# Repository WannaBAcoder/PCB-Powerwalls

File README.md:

# PCB-Powerwalls
This is the public file Repository for the [DIY PCB Powerwalls Community](https://www.facebook.com/groups/2573968699280898/). The projects are developed and maintained by **Vinnie Maro** and **Shaun Bond**.

We are developing a PCB alternative to common powerwall building techniques for 18650(and similar) batteries. This system has been developed with maintainability, expandability, and practicality in mind. 

For additional DIY Powerwall building resources, please check out some of the many other active facebook groups and forums:
* [DIY Powerwalls](https://www.facebook.com/groups/323586824654552/)
* [Jehu's DIY Powerwalls](https://www.facebook.com/groups/183620862292017/)
* [DIY Powerwall - easy](https://www.facebook.com/groups/244099703167519/)
* [Second Life Storage](https://secondlifestorage.com/index.php)

## Features in Development
To see features currently in development or exploration, check out our [issues](https://github.com/WannaBAcoder/PCB-Powerwalls/issues) page.

## 15s4p PCB

The 15s4p battery board is a stackable solution that reduces the amount of wiring required by placing all series and balance connections through standoffs that structurally connect the boards. Batteries mount to both sides of the PCB, in a variety of ways. Each cell is individually fused for added safety.

### 1. Plastic battery holders

You can choose to use plastic cell holders that are available in many through-hole and surface mount packages. For the through-hole packages, you must bend the pins at a 90 degree angle so that the holders sit as flat as possible.

### 2. Spring clips

A cheaper alternative to plastic holders is spring clips. The clips work like traditional battery holders with springs, but these require the use of zip ties to hold the cells in place.

### 3. Fuse wire

The last option is to use fuse wire. You will still need to use zip ties to hold the cells in place, but you can solder the fuse wire directly to the PCB pads, and remove the need for populating fuses(you will need to short the fuse pads to do this). You can also use large fuse wire and still use fuses, if desired. Spotwelding fuse wire to the batteries and soldering the other end to the PCB pads is recommended.

### 7s Adapter PCB

The 7s Adapter PCB was created to take our popular 15s4p design and convert it into a 7s8p PCB. We do this by leaving the out the 8s cells, which creates two 7s groups that get connected in parallel. It is recommended to use at least one of these adapter PCBs for every 5 boards, or 20A of main fuse(which is 10A load on each of these boards). This board also joins the battery stacks with standoffs. It's important to equally space these boards within a pack for best current distribution. For example, a 12 battery board stack could use 3 adapter boards, spaced every 4 boards.

### BMS/Display Adapter PCB

The BMS/display adapter board helps the user connect a [Moonitor](https://www.sarperonal.com/product/6s-16s-solar-plc-li-ion-battery-protection-system/), or a variety of BMS systems to the battery PCB stacks, and is capable of supporting ~5A balance current. This board also includes spaces to add series-level voltage displays, but they can be disabled if not desired.  You can also use this board with the 7s adapter board configurations.

## Building Your Own

### Ordering the PCBs

You can order your own boards from any number of PCB manufacturers. Many of our supporters use [JLCPCB.com](https://jlcpcb.com/quote).

**Recommended manufacturing options:**
* PCB thickness - 1.6mm
* PCB color-Your choice (black is not available for 2oz copper orders)
* Surface finish - HASL(with lead)
* Copper weight - 1oz or 2oz **(Higher current applications use 2oz)**
* All other options can be left as default

### Ordering Parts
#### Common Parts
* M4 Standoffs(40mm for SMD plastic holders, 45mm for through-hole plastic holders, may be able to make 40mm work with zip tie methods if zipties are alternated. Not confirmed at this time)
    -  [Nickel plated steel](https://www.aliexpress.com/item/33009686876.html?spm=a2g0o.productlist.0.0.61571f66pt5bWm&algo_pvid=9a643e7a-535f-40cf-b5ed-bd621be4c2a2&algo_expid=9a643e7a-535f-40cf-b5ed-bd621be4c2a2-38&btsid=cb015f28-81e7-4d5b-bff6-ac27e1b705c9&ws_ab_test=searchweb0_0%2Csearchweb201602_7%2Csearchweb201603_53&fbclid=IwAR1i7L36_8TP1QeeUUGsSI7OYQZ8V5TdpMY-vIQx72vAV06tubDgNu83XK8)
    - [Brass](https://www.aliexpress.com/item/32909068891.html?pid=808_0000_0109&spm=a2g0n.search-amp.list.32909068891&aff_trace_key=332c98827ee6446f80143395d597b19b-1564724741171-07852-UneMJZVf&aff_platform=msite&m_page_id=9849amp-ds4DZWQQ-IDu7HzwI4TLGw1564724838958&fbclid=IwAR3M15Ip61Iu9X8k-uB9fa5s9BZqdkEpw6nAfUjtFbnB0vwKfW6etgOFu9g)
    
* 60x Glass Axial Fuses
**Choosing the right fuse is based on tradeoff between usebility and saftey. Even a 0.5A fuse can't protect against all 18650(and similar) failure modes. Shaun Bond's testing suggests 0.5A fuses are the ideal size for safety, but impractical for all massive builds with low load. You should still consider your pack-loading characteristics when choosing them.**
  - [0.5A](https://www.ebay.com/itm/200Pcs-Glass-Fuse-Tube-Axial-With-Lead-Wire-Fast-Blows-Fuse-3x10mm-250V-0-5A-US-/283481427034?hash=item4200cf4c5a)
  - [1A](https://www.ebay.com/i/372678478703?chn=ps&norover=1&mkevt=1&mkrid=711-117182-37290-0&mkcid=2&itemid=372678478703&targetid=486560530718&device=m&mktype=pla&googleloc=9030145&poi=&campaignid=1497793114&mkgroupid=60383707360&rlsatarget=pla-486560530718&abcId=1139456&merchantid=137697764&gclid=EAIaIQobChMItaCEy6Dk4wIV0Rx9Ch3iWgGvEAQYCyABEgKVxPD_BwE&fbclid=IwAR1QAa1hm0T0Rmuvq4w6-hz3E788jz0vE18OvbbaAJsIOb30UHCT80PTtSM)
  - [1.5A](https://www.ebay.com/itm/200Pcs-Glass-Fuse-Tube-Axial-With-Lead-Wire-Fast-Blows-Fuse-3x10mm-250V-1-5A-P/401758396012?_trkparms=aid%3D555018%26algo%3DPL.SIM%26ao%3D2%26asc%3D20160908110712%26meid%3Da10f567fa4374be69fc06417b70cef45%26pid%3D100677%26rk%3D4%26rkt%3D30%26sd%3D333259318203%26itm%3D401758396012%26pg%3D2385738&_trksid=p2385738.c100677.m4598)
  - [2A](https://www.ebay.com/i/283303754606?rt=nc&_trkparms=aid%3D222007%26algo%3DSIM.MBE%26ao%3D2%26asc%3D20160908110712%26meid%3Da10f567fa4374be69fc06417b70cef45%26pid%3D100677%26rk%3D5%26rkt%3D30%26sd%3D333259318203%26itm%3D283303754606%26pg%3D2385738)
  - [3A](https://www.ebay.com/itm/200Pcs-Glass-Fuse-Tube-Axial-With-Lead-Wire-Fast-Blows-Fuse-3x10mm-250V-3A-US/283485834501?_trkparms=aid%3D555018%26algo%3DPL.SIM%26ao%3D2%26asc%3D20160908110712%26meid%3D45fd6583f6e14ab2a546fee1b4138e27%26pid%3D100677%26rk%3D1%26rkt%3D30%26sd%3D283303754606%26itm%3D283485834501%26pg%3D2385738&_trksid=p2385738.c100677.m4598)
  - [aliexpress](https://www.aliexpress.com/item/32910625856.html?spm=a2g0o.productlist.0.0.1737d2b4jAQsRa&algo_pvid=d670b6fe-927f-49bc-8e46-4ea88ec12f0d&algo_expid=d670b6fe-927f-49bc-8e46-4ea88ec12f0d-17&btsid=31c10488-12d2-4517-82d5-fce6cd9fe86a&ws_ab_test=searchweb0_0%2Csearchweb201602_7%2Csearchweb201603_53&fbclid=IwAR2cu_fARDCkvXmC-ECtJe0K4SezOG-_YxEne1wyviiZ2j2a6Mf_GHND5QM)
    
#### 15s4p PCB
**Be sure to choose the right holders for your desired build. For plastic holder builds, the quantities assume using only 1-cell and 2cell, or 3-cell and 4-cell holders per board. 
* Plastic Holders
  - 4x 1-cell holder([Keystone 1042](https://www.keyelco.com/product.cfm/product_id/918))
    - [mouser](https://www.mouser.com/ProductDetail/Keystone-Electronics/1042?qs=%2F7TOpeL5Mz4qPdWi9tuLKw%3D%3D&gclid=CjwKCAjwm4rqBRBUEiwAwaWjjC21kEPrcNO7SQeen5w2QoHVTzlL-M1gGIkDHi2yZwdU-rbxfRRc6xoCWLsQAvD_BwE)
    - [aliexpress](https://www.aliexpress.com/item/32843455571.html?spm=a2g0o.productlist.0.0.487c40e68pqd20&algo_pvid=2d7f9b9f-3d4c-4ce9-a35f-b65c2eb5f04f&algo_expid=2d7f9b9f-3d4c-4ce9-a35f-b65c2eb5f04f-0&btsid=5be8ef8c-3a87-41c8-af7c-a986ac64726d&ws_ab_test=searchweb0_0,searchweb201602_4,searchweb201603_52)

  - 28x 2-cell holder([Keystone 1048](https://www.keyelco.com/product.cfm/product_id/920)) 
    - [mouser](https://www.mouser.com/ProductDetail/Keystone-Electronics/1048?qs=%2F7TOpeL5Mz5jXkg8vI8Dyw%3D%3D)
    - [aliexpress](https://www.aliexpress.com/item/32810550974.html?spm=a2g0o.productlist.0.0.6d23509fdGDO8G&algo_pvid=bc697f71-8610-42bf-9caa-2c6182c8690e&algo_expid=bc697f71-8610-42bf-9caa-2c6182c8690e-0&btsid=5fac0df8-46fd-44b7-bddc-d52b5a4952c4&ws_ab_test=searchweb0_0,searchweb201602_4,searchweb201603_52)

  - 4x 3-cell holder(BK-18650-PC6)(through-hole)
    - [digikey](https://www.digikey.com/product-detail/en/mpd-memory-protection-devices/BK-18650-PC6/BK-18650-PC6-ND/2330514)
    - [aliexpress](https://www.aliexpress.com/item/32855470302.html?spm=a2g0o.productlist.0.0.26e322047uCJsr&algo_pvid=3ca87fa6-d69e-461c-b294-00b2a046b8a9&algo_expid=3ca87fa6-d69e-461c-b294-00b2a046b8a9-0&btsid=ad3d8f8d-a38c-414e-bdd7-eb4ffd6dbeee&ws_ab_test=searchweb0_0,searchweb201602_7,searchweb201603_53)

  - 24x 4-cell holder(BK-18650-PC8)(through-hole)
    - [digikey](https://www.digikey.com/product-detail/en/mpd-memory-protection-devices/BK-18650-PC8/BK-18650-PC8-ND/2330515)
    - [aliexpress](https://www.aliexpress.com/item/32813957846.html?spm=a2g0o.productlist.0.0.69dd44c0Jy70zY&algo_pvid=6d1f0285-86b4-4f30-8689-4ffc808e86bf&algo_expid=6d1f0285-86b4-4f30-8689-4ffc808e86bf-0&btsid=38b36ad8-3752-4109-9ae1-f03aeb2c26e8&ws_ab_test=searchweb0_0,searchweb201602_7,searchweb201603_53)
       
* 120x Spring clips([Keystone 5331](https://www.keyelco.com/product.cfm/product_id/823))
    - [mouser](https://www.mouser.com/ProductDetail/Keystone-Electronics/5331?qs=poiiR8sYdC9oC9Ij8wI9kA%3D%3D)
    - [newark](https://www.newark.com/keystone/5331/battery-contact-a-aa-2-3a-cell/dp/25T0473)
 
#### BMS/Display Adapter PCB
* 1x Total voltage pack voltage display(Adafruit 705)
    - [mouser](https://www.digikey.com/products/en/industrial-automation-and-controls/panel-meters/805?k=adafruit%20705)
    - [Adafruit](https://www.adafruit.com/product/705
    
* 15x Series-group voltage display(Seeed 114990163)
    - [mouser](https://www.mouser.com/ProductDetail/Seeed-Studio/114990163?qs=%2Fha2pyFaduhQJK%2FIqB6h3cWbaw8mrLdet0cfTARQbUci7a%252BfqW62TQ%3D%3D)
    - [Seeed](https://www.seeedstudio.com/0-28-Inch-LED-digital-DC-voltmeter-Green-p-2287.html)
    - [Digikey](https://www.digikey.com/products/en/industrial-automation-and-controls/panel-meters/805?k=&pkeyword=&sv=0&v=1597&pv1989=0&sf=0&FV=ffe00325&quantity=&ColumnSort=0&page=1&stock=1&pageSize=25) has other colors too.
    
* 1x 12VDC 40x40mm PC Fan(2-wire)
    - Tons of these on [Amazon](https://www.amazon.com/WINSINN-Brushless-40x40x10mm-Extruder-Makerbot/dp/B0757LXKST/ref=sr_1_3?keywords=12v+40mm+fan&qid=1564763803&s=gateway&sr=8-3)

* 1x 75VDC to 12V buck converter module.
    - [mouser](https://www.mouser.com/ProductDetail/XP-Power/SRH05S12?qs=%2Fha2pyFadugN%252BYt0642c137FJqBA04EEkA%252BHmhjnYgQ%3D)
    - [Digikey](https://www.digikey.com/products/en?keywords=srh05s12)
    
* 1x 0.25A glass fuse
    - [Digikey](https://www.digikey.com/product-detail/en/littelfuse-inc/0251.250NRT1L/F5997CT-ND/4146349)
    - [mouser](https://www.mouser.com/ProductDetail/Littelfuse/0251250NRT1L?qs=%2Fha2pyFadugfDk6tKwZ2TFq2EME7Ea%252Bx7IV62g8M4POuyu4j1eOqCA%3D%3D)
    - [Ebay](https://www.ebay.com/itm/200Pc-Glass-Tube-Fuse-Metal-Axial-Double-Hat-Fast-Blow-Fuse-3-6x10mm-250V-0-25A/264389811818?epid=2270852170&hash=item3d8edc5e6a:g:CDoAAOSwokVdIOIx)

* 16x B4A Lugs
    - [hex](https://lugsdirect.com/B4A-PCB-HEX.html)
    
* 0.1" male pin headers
    - [aliexpress](https://www.aliexpress.com/item/32899255706.html?spm=a2g0o.productlist.0.0.6a13532boQDFkx&algo_pvid=8dbb68db-2cf8-45e3-86e2-01a316cf7929&algo_expid=8dbb68db-2cf8-45e3-86e2-01a316cf7929-8&btsid=413ff5c7-b166-4259-ab24-a0d8e013eebf&ws_ab_test=searchweb0_0,searchweb201602_7,searchweb201603_53)
    
* 0.1" jumper blocks
    - [aliexpress](https://www.aliexpress.com/item/32972892184.html?spm=a2g0o.productlist.0.0.679cd873JeFb6B&s=p&algo_pvid=b014d28b-b7de-4ef0-ac41-d2149ee41d24&algo_expid=b014d28b-b7de-4ef0-ac41-d2149ee41d24-5&btsid=e50a15f9-9d8d-4b6d-bcb8-219688b9c177&ws_ab_test=searchweb0_0,searchweb201602_7,searchweb201603_53)
 
* Moonitor BMS

You can purchase this BMS from the Moonitor team on their [website](https://www.sarperonal.com/product/6s-16s-solar-plc-li-ion-battery-protection-system/). You can also contact [them](https://www.sarperonal.com/contact-us/) directly for more information.

### Building Instructions and Documentation
Check out the [wiki](https://github.com/WannaBAcoder/PCB-Powerwalls/wiki) for assembly instructions, and additional information.

## Versioning

Each powerwall PCB has its own revision in the form of VX.X. In addition to this, we version the entire system package in a release in the form of RX.0. See the latest release for the most recent hardware package. Whenever any of the hardware in a package changes, the PCB version and package release will be updated. PCB versions are printed on all PCBs for easy identification.

## Contributing

Although the kicad source files are available, the safety considerations that go into this project make it potentially unsafe to modify; do so at your own risk! You can always contribute to the development of this project by suggesting improvements or new features desired by reporting them as [issues](https://github.com/WannaBAcoder/PCB-Powerwalls/issues).

## License

This project is licensed under the CERN Open Hardware License - see the [LICENSE.txt](LICENSE.txt) file for details.

## Acknowledgments

A special thank you to the people and communities that inspired or helped develop the early versions of this hardware and helped others realize the growing potential for these designs:
* Shaun Bond
* Izz Eselam
* Paulo E Cabigao
* Dale Bliss
* Jehu Garcia 
* Andrew Hunt
* Daniel Wiermans

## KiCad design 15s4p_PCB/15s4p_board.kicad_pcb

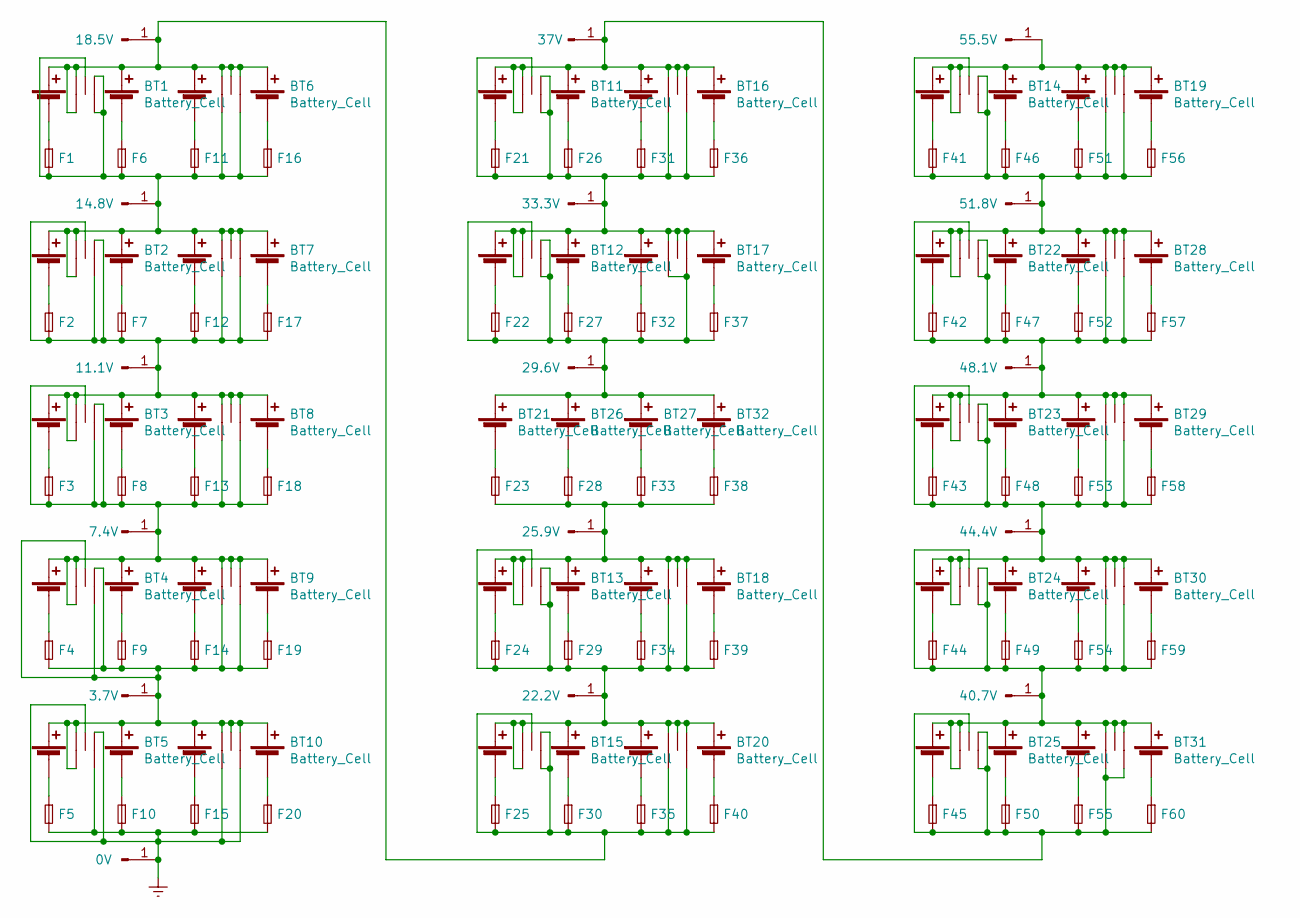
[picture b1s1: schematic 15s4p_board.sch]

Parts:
BT1, BT2, BT3, BT4, BT5, BT6, BT7, BT8, BT9, BT10, BT11, BT12, BT13, BT14, BT15, BT16, BT17, BT18, BT19, BT20, BT22, BT23, BT24, BT25, BT28, BT29, BT30, BT31: Battery_Cell; 2cell_dual_holder_longer
BT21, BT26, BT27, BT32: Battery_Cell; single_cell_dual_holder
F1, F2, F3, F4, F5, F6, F7, F8, F9, F10, F11, F12, F13, F14, F15, F16, F17, F18, F19, F20, F21, F22, F23, F24, F25, F26, F27, F28, F29, F30, F31, F32, F33, F34, F35, F36, F37, F38, F39, F40, F41, F42, F43, F44, F45, F46, F47, F48, F49, F50, F51, F52, F53, F54, F55, F56, F57, F58, F59, F60: Fuse_Small; fuse
J1: 18.5V; hole
J2: 14.8V; hole
J3: 11.1V; hole
J4: 7.4V; hole
J5: 3.7V; hole
J6: 0V; hole
J7: 37V; hole
J8: 33.3V; hole
J9: 29.6V; hole
J10: 25.9V; hole
J11: 22.2V; hole
J12: 55.5V; hole
J13: 51.8V; hole
J14: 48.1V; hole
J15: 44.4V; hole
J16: 40.7V; hole

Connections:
Earth: BT5.6 (rr), BT5.8, BT5.9, BT10.5 (f), BT10.6 (rr), F5.2, F10.2, F15.2, F20.2, J6.1
unnamed: BT1.1 (+), BT1.3 (+), BT1.5 (f), BT1.7 (tt), BT6.1 (+), BT6.3 (+), BT6.7 (tt), BT6.8, BT6.9, BT15.6 (rr), BT15.8, BT15.9, BT20.5 (f), BT20.6 (rr), F25.2, F30.2, F35.2, F40.2, J1.1
unnamed: BT1.2 (-), F1.1
unnamed: BT1.4 (-), F6.1
unnamed: BT1.6 (rr), BT1.8, BT1.9, BT2.1 (+), BT2.3 (+), BT2.5 (f), BT2.7 (tt), BT6.5 (f), BT6.6 (rr), BT7.1 (+), BT7.3 (+), BT7.7 (tt), BT7.8, BT7.9, F1.2, F6.2, F11.2, F16.2, J2.1
unnamed: BT2.2 (-), F2.1
unnamed: BT2.4 (-), F7.1
unnamed: BT2.6 (rr), BT2.8, BT2.9, BT3.1 (+), BT3.3 (+), BT3.5 (f), BT3.7 (tt), BT7.5 (f), BT7.6 (rr), BT8.1 (+), BT8.3 (+), BT8.7 (tt), BT8.8, BT8.9, F2.2, F7.2, F12.2, F17.2, J3.1
unnamed: BT3.2 (-), F3.1
unnamed: BT3.4 (-), F8.1
unnamed: BT3.6 (rr), BT3.8, BT3.9, BT4.1 (+), BT4.3 (+), BT4.5 (f), BT4.7 (tt), BT8.5 (f), BT8.6 (rr), BT9.1 (+), BT9.3 (+), BT9.7 (tt), BT9.8, BT9.9, F3.2, F8.2, F13.2, F18.2, J4.1
unnamed: BT4.2 (-), F4.1
unnamed: BT4.4 (-), F9.1
unnamed: BT5.2 (-), F5.1
unnamed: BT5.4 (-), F10.1
unnamed: BT6.2 (-), F11.1
unnamed: BT6.4 (-), F16.1
unnamed: BT7.2 (-), F12.1
unnamed: BT7.4 (-), F17.1
unnamed: BT8.2 (-), F13.1
unnamed: BT8.4 (-), F18.1
unnamed: BT9.2 (-), F14.1
unnamed: BT9.4 (-), F19.1
unnamed: BT4.6 (rr), BT4.8, BT4.9, BT5.1 (+), BT5.3 (+), BT5.5 (f), BT5.7 (tt), BT9.5 (f), BT9.6 (rr), BT10.1 (+), BT10.3 (+), BT10.7 (tt), BT10.8, BT10.9, F4.2, F9.2, F14.2, F19.2, J5.1
unnamed: BT10.2 (-), F15.1
unnamed: BT10.4 (-), F20.1
unnamed: BT11.1 (+), BT11.3 (+), BT11.5 (f), BT11.7 (tt), BT16.1 (+), BT16.3 (+), BT16.7 (tt), BT16.8, BT16.9, BT25.6 (rr), BT25.8, BT25.9, BT31.5 (f), BT31.6 (rr), F45.2, F50.2, F55.2, F60.2, J7.1
unnamed: BT11.2 (-), F21.1
unnamed: BT11.4 (-), F26.1
unnamed: BT11.6 (rr), BT11.8, BT11.9, BT12.1 (+), BT12.3 (+), BT12.5 (f), BT12.7 (tt), BT16.5 (f), BT16.6 (rr), BT17.1 (+), BT17.3 (+), BT17.7 (tt), BT17.8, BT17.9, F21.2, F26.2, F31.2, F36.2, J8.1
unnamed: BT12.2 (-), F22.1
unnamed: BT12.4 (-), F27.1
unnamed: BT13.2 (-), F24.1
unnamed: BT13.4 (-), F29.1
unnamed: BT13.6 (rr), BT13.8, BT13.9, BT15.1 (+), BT15.3 (+), BT15.5 (f), BT15.7 (tt), BT18.5 (f), BT18.6 (rr), BT20.1 (+), BT20.3 (+), BT20.7 (tt), BT20.8, BT20.9, F24.2, F29.2, F34.2, F39.2, J11.1
unnamed: BT14.1 (+), BT14.3 (+), BT14.5 (f), BT14.7 (tt), BT19.1 (+), BT19.3 (+), BT19.7 (tt), BT19.8, BT19.9, J12.1
unnamed: BT14.2 (-), F41.1
unnamed: BT14.4 (-), F46.1
unnamed: BT14.6 (rr), BT14.8, BT14.9, BT19.5 (f), BT19.6 (rr), BT22.1 (+), BT22.3 (+), BT22.5 (f), BT22.7 (tt), BT28.1 (+), BT28.3 (+), BT28.7 (tt), BT28.8, BT28.9, F41.2, F46.2, F51.2, F56.2, J13.1
unnamed: BT15.2 (-), F25.1
unnamed: BT15.4 (-), F30.1
unnamed: BT16.2 (-), F31.1
unnamed: BT16.4 (-), F36.1
unnamed: BT17.2 (-), F32.1
unnamed: BT17.4 (-), F37.1
unnamed: BT18.2 (-), F34.1
unnamed: BT18.4 (-), F39.1
unnamed: BT19.2 (-), F51.1
unnamed: BT19.4 (-), F56.1
unnamed: BT20.2 (-), F35.1
unnamed: BT20.4 (-), F40.1
unnamed: BT21.2 (-), F23.1
unnamed: BT22.2 (-), F42.1
unnamed: BT22.4 (-), F47.1
unnamed: BT22.6 (rr), BT22.8, BT22.9, BT23.1 (+), BT23.3 (+), BT23.5 (f), BT23.7 (tt), BT28.5 (f), BT28.6 (rr), BT29.1 (+), BT29.3 (+), BT29.7 (tt), BT29.8, BT29.9, F42.2, F47.2, F52.2, F57.2, J14.1
unnamed: BT23.2 (-), F43.1
unnamed: BT23.4 (-), F48.1
unnamed: BT23.6 (rr), BT23.8, BT23.9, BT24.1 (+), BT24.3 (+), BT24.5 (f), BT24.7 (tt), BT29.5 (f), BT29.6 (rr), BT30.1 (+), BT30.3 (+), BT30.7 (tt), BT30.8, BT30.9, F43.2, F48.2, F53.2, F58.2, J15.1
unnamed: BT24.2 (-), F44.1
unnamed: BT24.4 (-), F49.1
unnamed: BT24.6 (rr), BT24.8, BT24.9, BT25.1 (+), BT25.3 (+), BT25.5 (f), BT25.7 (tt), BT30.5 (f), BT30.6 (rr), BT31.1 (+), BT31.3 (+), BT31.7 (tt), BT31.8, BT31.9, F44.2, F49.2, F54.2, F59.2, J16.1
unnamed: BT25.2 (-), F45.1
unnamed: BT25.4 (-), F50.1
unnamed: BT26.2 (-), F28.1
unnamed: BT27.2 (-), F33.1
unnamed: BT28.2 (-), F52.1
unnamed: BT28.4 (-), F57.1
unnamed: BT29.2 (-), F53.1
unnamed: BT29.4 (-), F58.1
unnamed: BT30.2 (-), F54.1
unnamed: BT30.4 (-), F59.1
unnamed: BT31.2 (-), F55.1
unnamed: BT31.4 (-), F60.1
unnamed: BT32.2 (-), F38.1

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
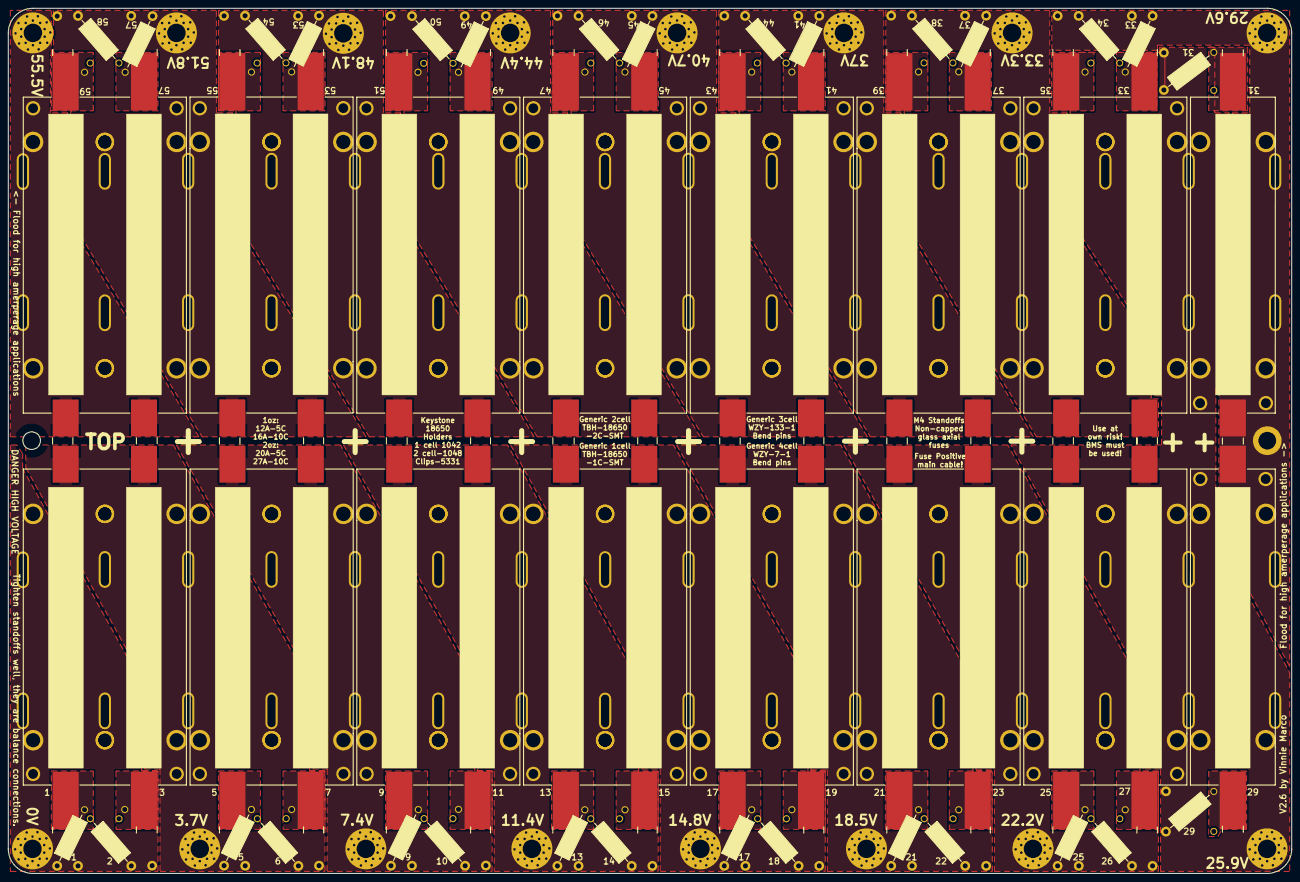
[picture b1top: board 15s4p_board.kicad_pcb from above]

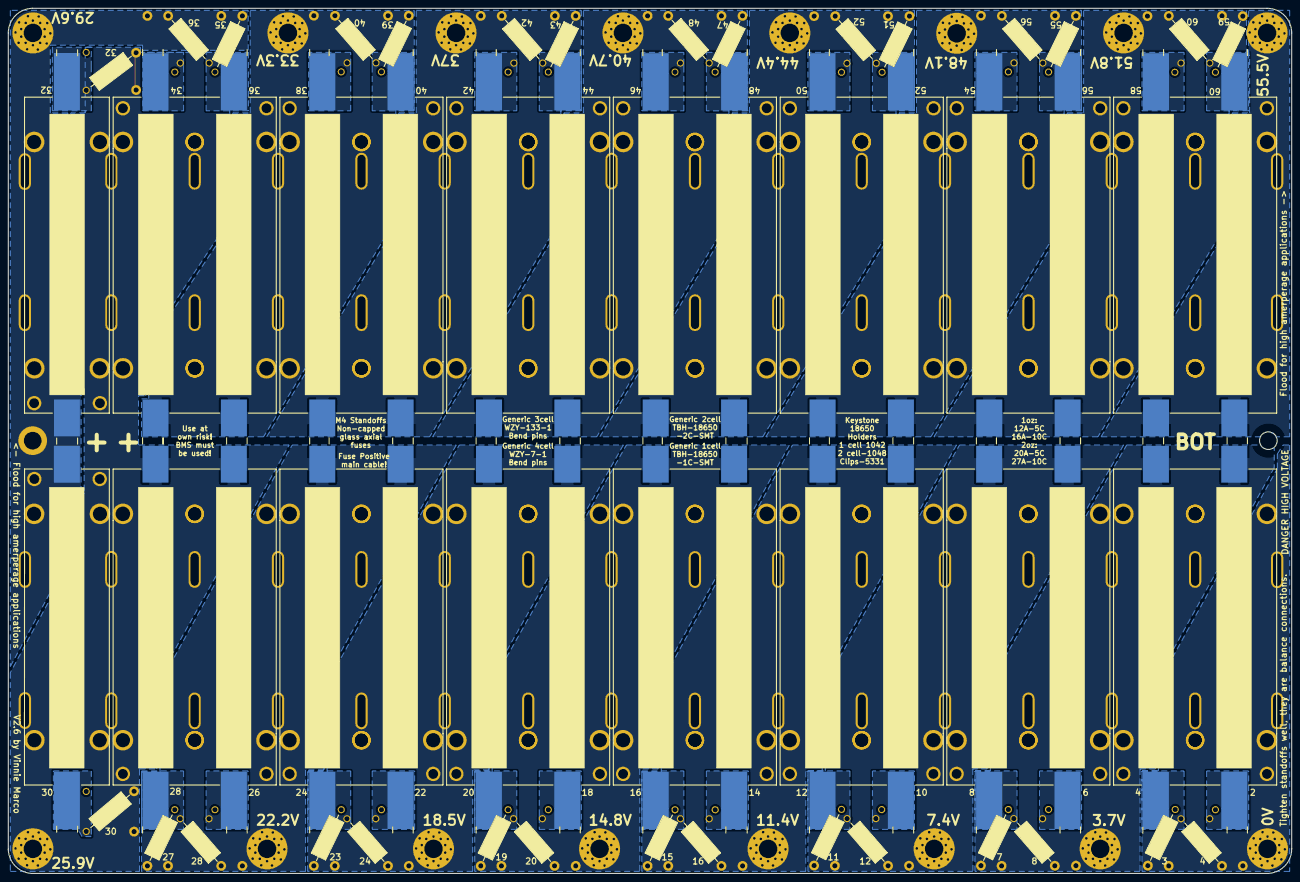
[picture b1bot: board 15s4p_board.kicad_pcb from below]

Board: 2 copper layers, 313.0 x 211.0 mm, 108 parts (46 on the bottom side), 76 nets.

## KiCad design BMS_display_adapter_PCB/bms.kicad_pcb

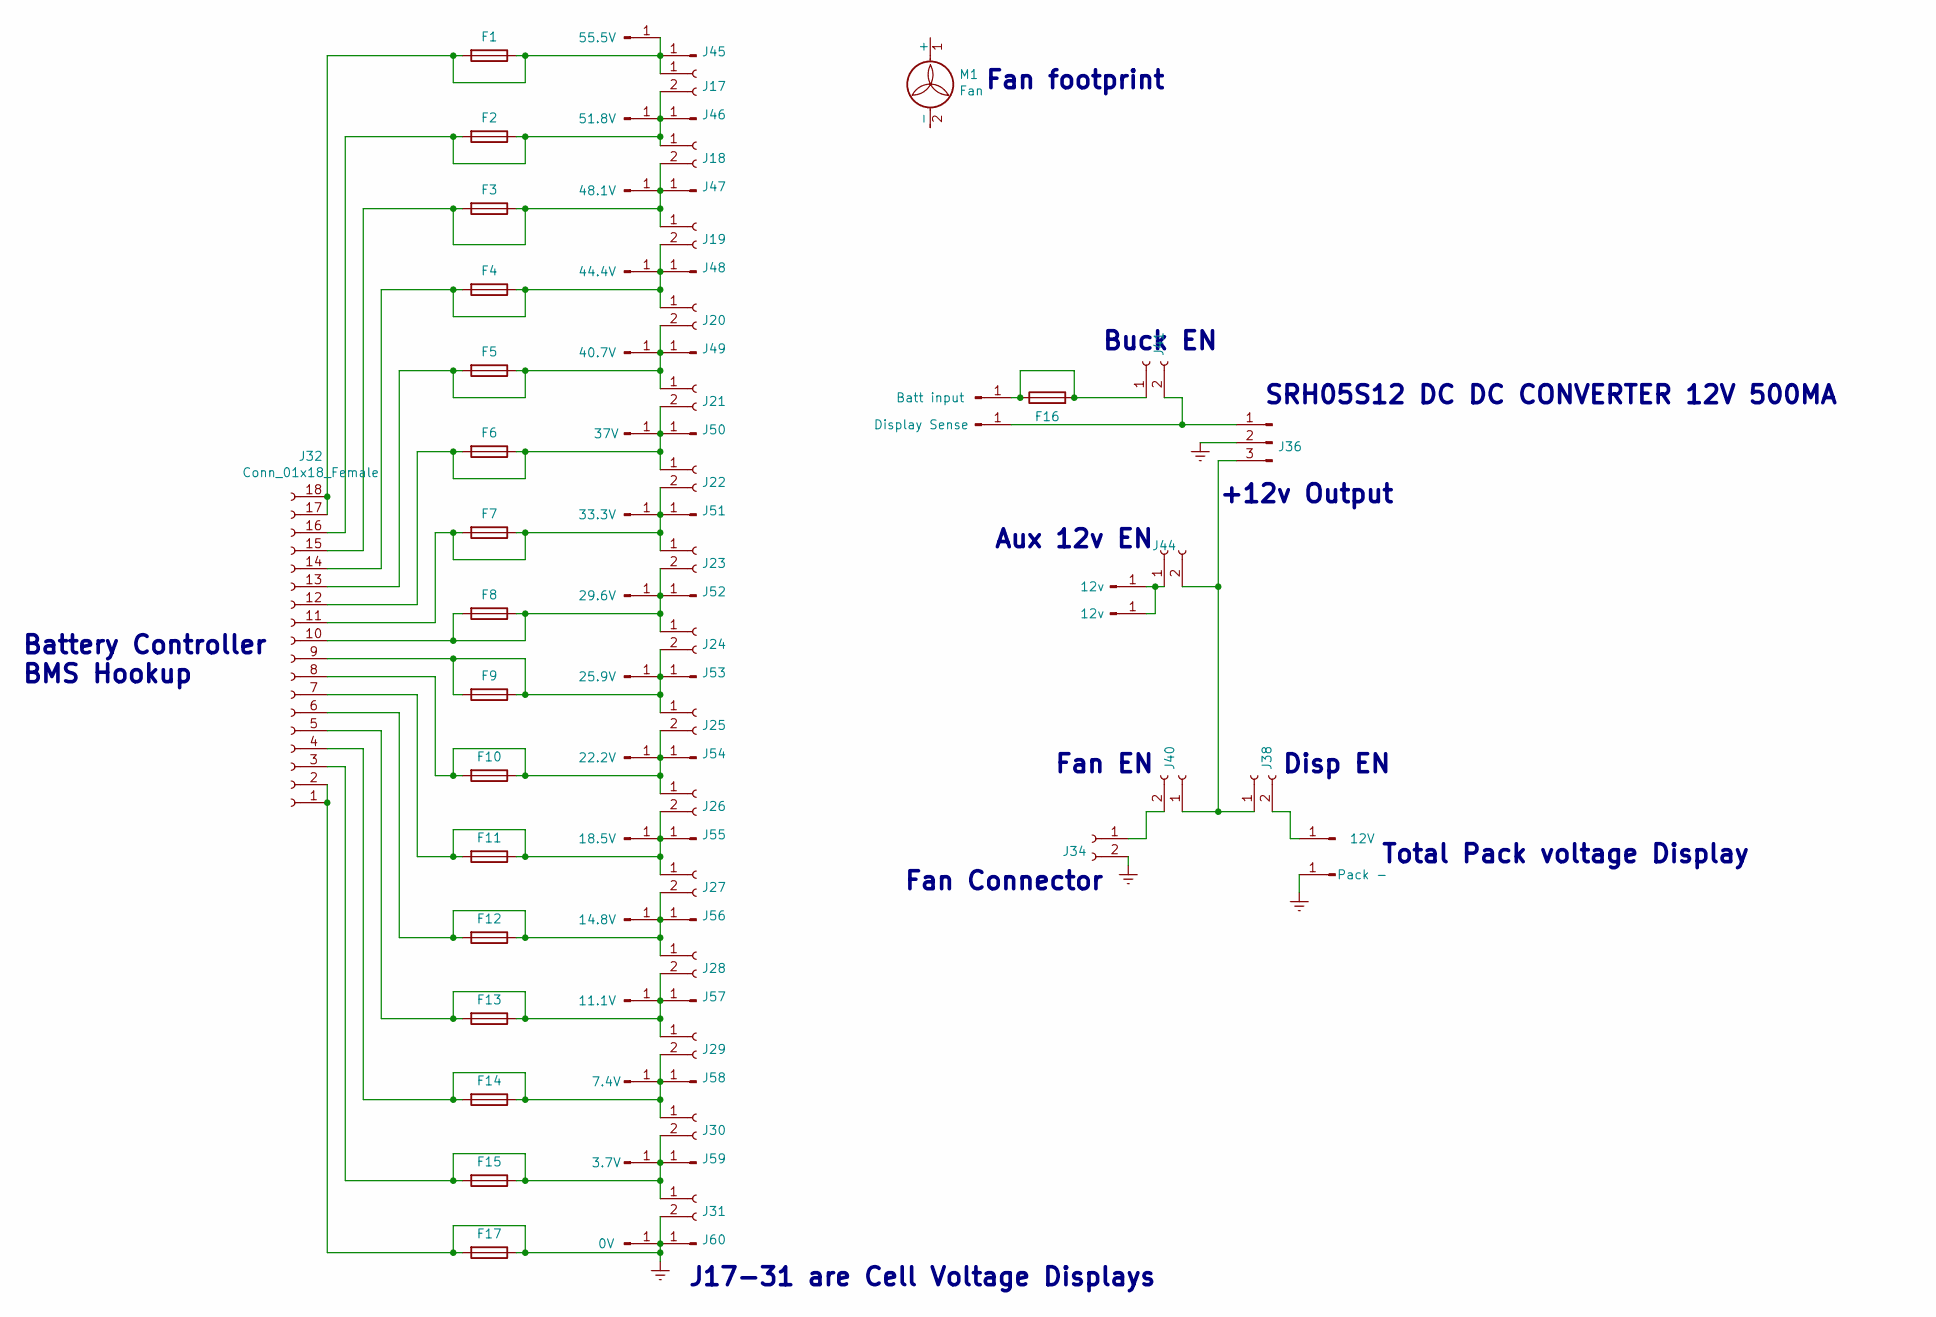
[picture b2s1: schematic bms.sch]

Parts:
F1, F2, F3, F4, F5, F6, F7, F8, F9, F10, F11, F12, F13, F14, F15, F16, F17: Fuse
J1: 55.5V; hole
J2: 51.8V; hole
J3: 48.1V; hole
J4: 44.4V; hole
J5: 40.7V; hole
J6: 37V; hole
J7: 33.3V; hole
J8: 29.6V; hole
J9: 25.9V; hole
J10: 22.2V; hole
J11: 18.5V; hole
J12: 14.8V; hole
J13: 11.1V; hole
J14: 7.4V; hole
J15: 3.7V; hole
J16: 0V; hole
J17, J18, J19, J20, J21, J22, J23, J24, J25, J26, J27, J28, J29, J30, J31: Conn_01x02_Female; VoltMeter
J32: Conn_01x18_Female; BMS_module
J33: Display Sense; hole
J34: Conn_01x02_Female; fan_holes
J35: 12V; hole
J36: Conn_01x03_Male; Buck converter
J37: Pack -; hole
J38, J40, J41, J44: Conn_01x02_Female; jumper
J39: Batt input; hole
J42, J43: 12v; hole
J45, J46, J47, J48, J49, J50, J51, J52, J53, J54, J55, J56, J57, J58, J59, J60: Conn_01x01_Male; B4A-PCB
M1: Fan; 40mm_fan

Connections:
Earth: F17.1, F17.2, J16.1, J31.2, J32.1, J32.2, J34.2, J36.2, J37.1, J60.1
unnamed: F1.1, F1.2, J1.1, J17.1, J32.17, J32.18, J45.1
unnamed: F2.1, F2.2, J2.1, J17.2, J18.1, J32.16, J46.1
unnamed: F3.1, F3.2, J3.1, J18.2, J19.1, J32.15, J47.1
unnamed: F4.1, F4.2, J4.1, J19.2, J20.1, J32.14, J48.1
unnamed: F5.1, F5.2, J5.1, J20.2, J21.1, J32.13, J49.1
unnamed: F6.1, F6.2, J6.1, J21.2, J22.1, J32.12, J50.1
unnamed: F7.1, F7.2, J7.1, J22.2, J23.1, J32.11, J51.1
unnamed: F8.1, F8.2, J8.1, J23.2, J24.1, J32.10, J52.1
unnamed: F9.1, F9.2, J9.1, J24.2, J25.1, J32.9, J53.1
unnamed: F10.1, F10.2, J10.1, J25.2, J26.1, J32.8, J54.1
unnamed: F11.1, F11.2, J11.1, J26.2, J27.1, J32.7, J55.1
unnamed: F12.1, F12.2, J12.1, J27.2, J28.1, J32.6, J56.1
unnamed: F13.1, F13.2, J13.1, J28.2, J29.1, J32.5, J57.1
unnamed: F14.1, F14.2, J14.1, J29.2, J30.1, J32.4, J58.1
unnamed: F15.1, F15.2, J15.1, J30.2, J31.1, J32.3, J59.1
unnamed: F16.1, F16.2, J39.1, J41.1
unnamed: J33.1, J36.1, J41.2
unnamed: J34.1, J40.2
unnamed: J35.1, J38.2
unnamed: J36.3, J38.1, J40.1, J44.2
unnamed: J42.1, J43.1, J44.1

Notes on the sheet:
Total Pack voltage Display
J17-31 are Cell Voltage Displays
Battery Controller BMS Hookup
SRH05S12 DC DC CONVERTER 12V 500MA
Disp EN
Buck EN
Aux 12v EN
+12v Output
Fan footprint
Fan Connector
Fan EN

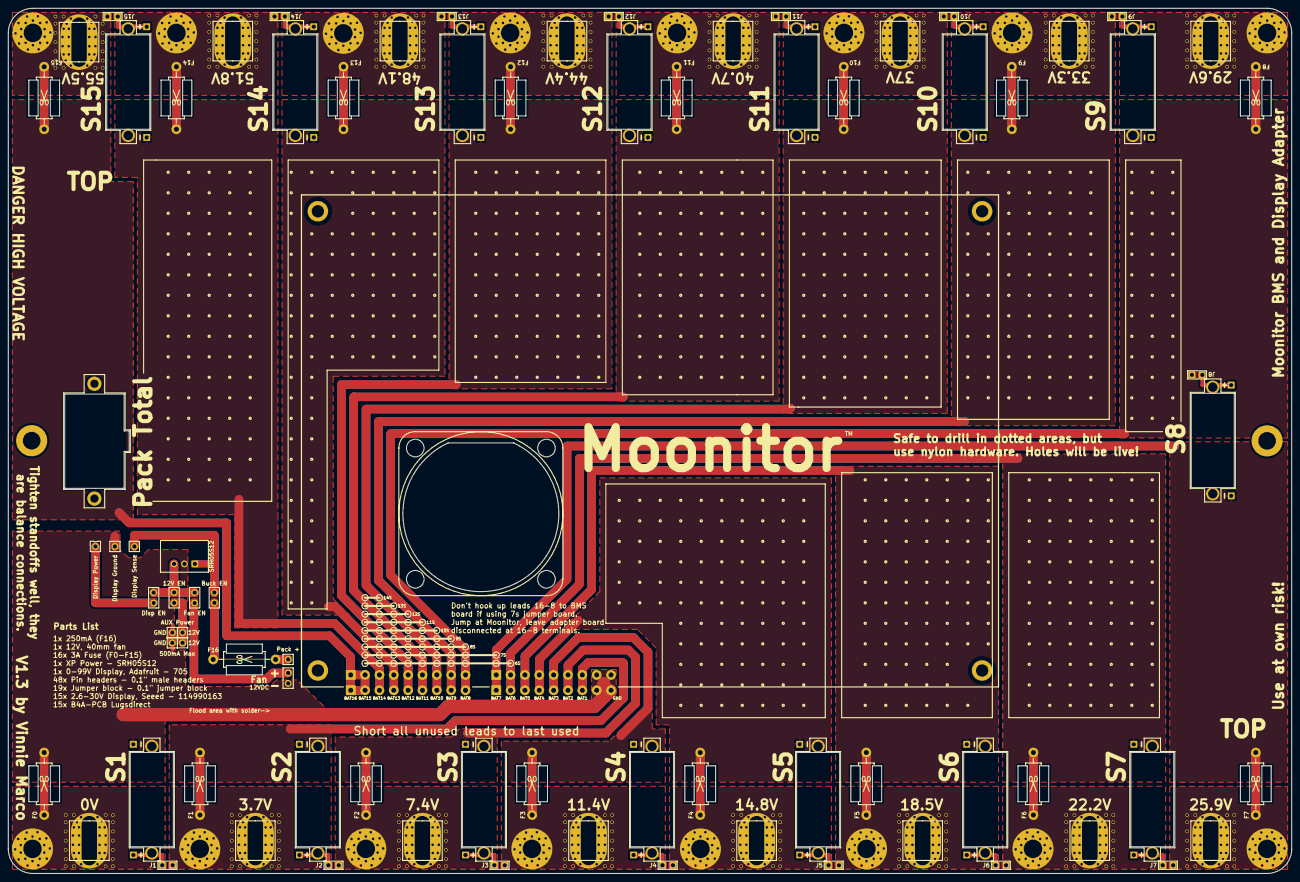
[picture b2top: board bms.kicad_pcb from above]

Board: 2 copper layers, 313.0 x 211.0 mm, 78 parts (0 on the bottom side), 22 nets.

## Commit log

2019-07-31 V1.0 Release
2019-07-31 V2.4 Release
    First public release of 15s4p PCB
2019-07-31 V1.1 Release
    First public release of the BMS/Display Adapter PCB
2019-07-31 R1.0
    First public package release
2019-08-01 Create LICENSE.txt
    Add CERN OHL V1.2 License
2019-08-01 Update README.md
    updating readme
2019-08-06 adding screw terminals
2019-08-06 work
2019-08-08 moving displays to make room for lugs
2019-08-08 redrawing planes
2019-08-09 footprint updates
2019-08-13 V1.2 Release
2019-08-13 V1.1 Release
    Increased standoff hole size and via layout
2019-08-13 V1.1 Release
2019-08-13 V2.5 Release
    updated standoff pads
2019-08-13 V1.2 Release
    Updated standoff mounting holes
2019-08-13 V1.2 Release
    mvoed gerbers to zip file
2019-08-13 updated 3d models
2019-08-13 R2.0 Package Release
2019-08-14 V2.6 Release
2019-08-14 fixed save-file issue
2019-09-12 V1.3 updates
2019-09-12 V1.3 Release
2019-09-12 Updated Flood Mask
2019-09-12 R3.0 Package Release
